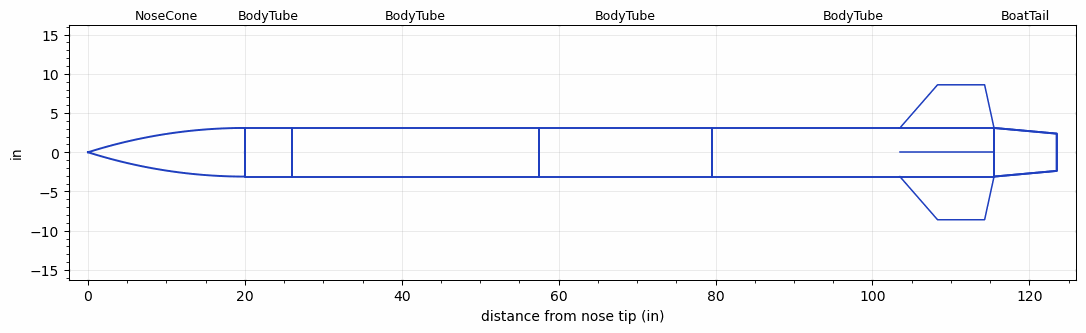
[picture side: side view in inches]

<RASAeroDocument>
 <FileVersion>2</FileVersion>
 <RocketDesign>
  <NoseCone>
   <Length>20</Length>
   <Diameter>6.2</Diameter>
   <Shape>Tangent Ogive</Shape>
   <Location>0</Location>
  </NoseCone>
  <BodyTube>
   <Length>6</Length>
   <Diameter>6.2</Diameter>
   <Location>20</Location>
  </BodyTube>
  <BodyTube>
   <Length>31.4999</Length>
   <Diameter>6.2</Diameter>
   <Location>25.9999</Location>
  </BodyTube>
  <BodyTube>
   <Length>22</Length>
   <Diameter>6.2</Diameter>
   <RailGuideDiameter>0.62</RailGuideDiameter>
   <RailGuideHeight>0.4495</RailGuideHeight>
   <Location>57.4999</Location>
  </BodyTube>
  <BodyTube>
   <Length>35.9999</Length>
   <Diameter>6.2</Diameter>
   <RailGuideDiameter>0.62</RailGuideDiameter>
   <RailGuideHeight>0.4495</RailGuideHeight>
   <Location>79.4998</Location>
   <BoattailLength>8</BoattailLength>
   <BoattailRearDiameter>4.75</BoattailRearDiameter>
   <Fin>
    <Count>4</Count>
    <Chord>12</Chord>
    <Span>5.5</Span>
    <SweepDistance>4.8</SweepDistance>
    <TipChord>6</TipChord>
    <Thickness>0.1875</Thickness>
    <Location>12</Location>
    <AirfoilSection>Rounded</AirfoilSection>
   </Fin>
  </BodyTube>
  <BoatTail>
   <Length>8</Length>
   <Diameter>6.2</Diameter>
   <RearDiameter>4.75</RearDiameter>
   <Location>115.4998</Location>
  </BoatTail>
  <Surface>Rough Camouflage Paint</Surface>
  <ModifiedBarrowman>False</ModifiedBarrowman>
  <Turbulence>False</Turbulence>
  <UseBooster1>False</UseBooster1>
  <UseBooster2>False</UseBooster2>
 </RocketDesign>
 <LaunchSite>
  <Altitude>2930</Altitude>
  <Pressure>27.0263</Pressure>
  <RodAngle>6</RodAngle>
  <RodLength>148.4997</RodLength>
  <Temperature>80</Temperature>
  <WindSpeed>15</WindSpeed>
 </LaunchSite>
 <Recovery>
  <Altitude1>1312.336</Altitude1>
  <Altitude2>0</Altitude2>
  <DeviceType1>Parachute</DeviceType1>
  <DeviceType2>None</DeviceType2>
  <Event1>True</Event1>
  <Event2>False</Event2>
  <Size1>95.9998</Size1>
  <Size2>0</Size2>
  <EventType1>Altitude</EventType1>
  <EventType2>None</EventType2>
  <CD1>2.2</CD1>
  <CD2>0</CD2>
 </Recovery>
 <SimulationList>
  <Simulation>
   <SustainerEngine>M6000ST  (AT)</SustainerEngine>
   <SustainerLaunchWt>67.5</SustainerLaunchWt>
   <SustainerCG>70.75</SustainerCG>
   <SustainerIgnitionDelay>0</SustainerIgnitionDelay>
   <Booster1SeparationDelay>0</Booster1SeparationDelay>
   <Booster1IgnitionDelay>0</Booster1IgnitionDelay>
   <IncludeBooster1>False</IncludeBooster1>
   <Booster2Delay>0</Booster2Delay>
   <IncludeBooster2>False</IncludeBooster2>
   <TimetoApogee>24.78047</TimetoApogee>
   <MaxAltitude>10686.45</MaxAltitude>
   <MaxVelocity>1026.422</MaxVelocity>
  </Simulation>
 </SimulationList>
</RASAeroDocument>
